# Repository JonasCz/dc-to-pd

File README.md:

# 10 - 60v input 60w DC to USB-C PD buck-boost converter module using TPS25740B and LM5118

**Status:** 

works, but **poor performance**: excessive (maybe - ?) ripple, especially in boost mode and at higher power levels. Mac laptop charges sucessfully off of it, sometimes. Diodes and inductor heats too much (80c at full load). This might be a straightforward fix, or a more siginficant design error (wrong component choice, values, or layout...)

**Why:**

The goal is that I can charge my laptop off an ebike battery directly, or any other DC source (solar system). No other solution that accepts this high input voltage in existence when I started this, now there is YZ826S from china which does the same thing (which I'll try before continueing to work on this project).

**Prototype:**

**Features:**

* Done in Kicad 6.
* Single-sided board for easy assembly.
* The single-sidedness means that it may be possible in a future revision to replace the remaining THT parts with SMD, and then attach a heatsink or enclosure to the back, for through-the-board cooling.
* As compact as possible.
* Input protection:
     * Reverse-polarity protection provided by two high-side n-channel mosfets back-to-back, driven by HT0440.
     * Inrush current limiting provided by same mosfets, by slowing the switch-on speed significantly.
     * Fuse
     * both of these work well, I will reuse this in other designs.
* Low standby / idle power consumption: the buck-boost converter is disabled when no device (power consumer) connected.
* Adjustable low-voltage cutout.
* Datasheet implementations for TPS25740B and LM5118 are mostly folowed, only the input protection, 5v supply, and power-saving stuff has some clever stuff.
* XT60 power connectors.
* Status indicator LED.

**Warning:** 

TPS25740B seems to be discontinued with no obvious replacement. I had to buy them on Aliexpress. Has some minor bugs (I forgot what exactly. Notably needs an additional / different mosfet somewhere. I'll update this when I find my prototype board where I bodged it on. Also requires one cap around LM5118 replaced with different value).

Play with this at your own risk..

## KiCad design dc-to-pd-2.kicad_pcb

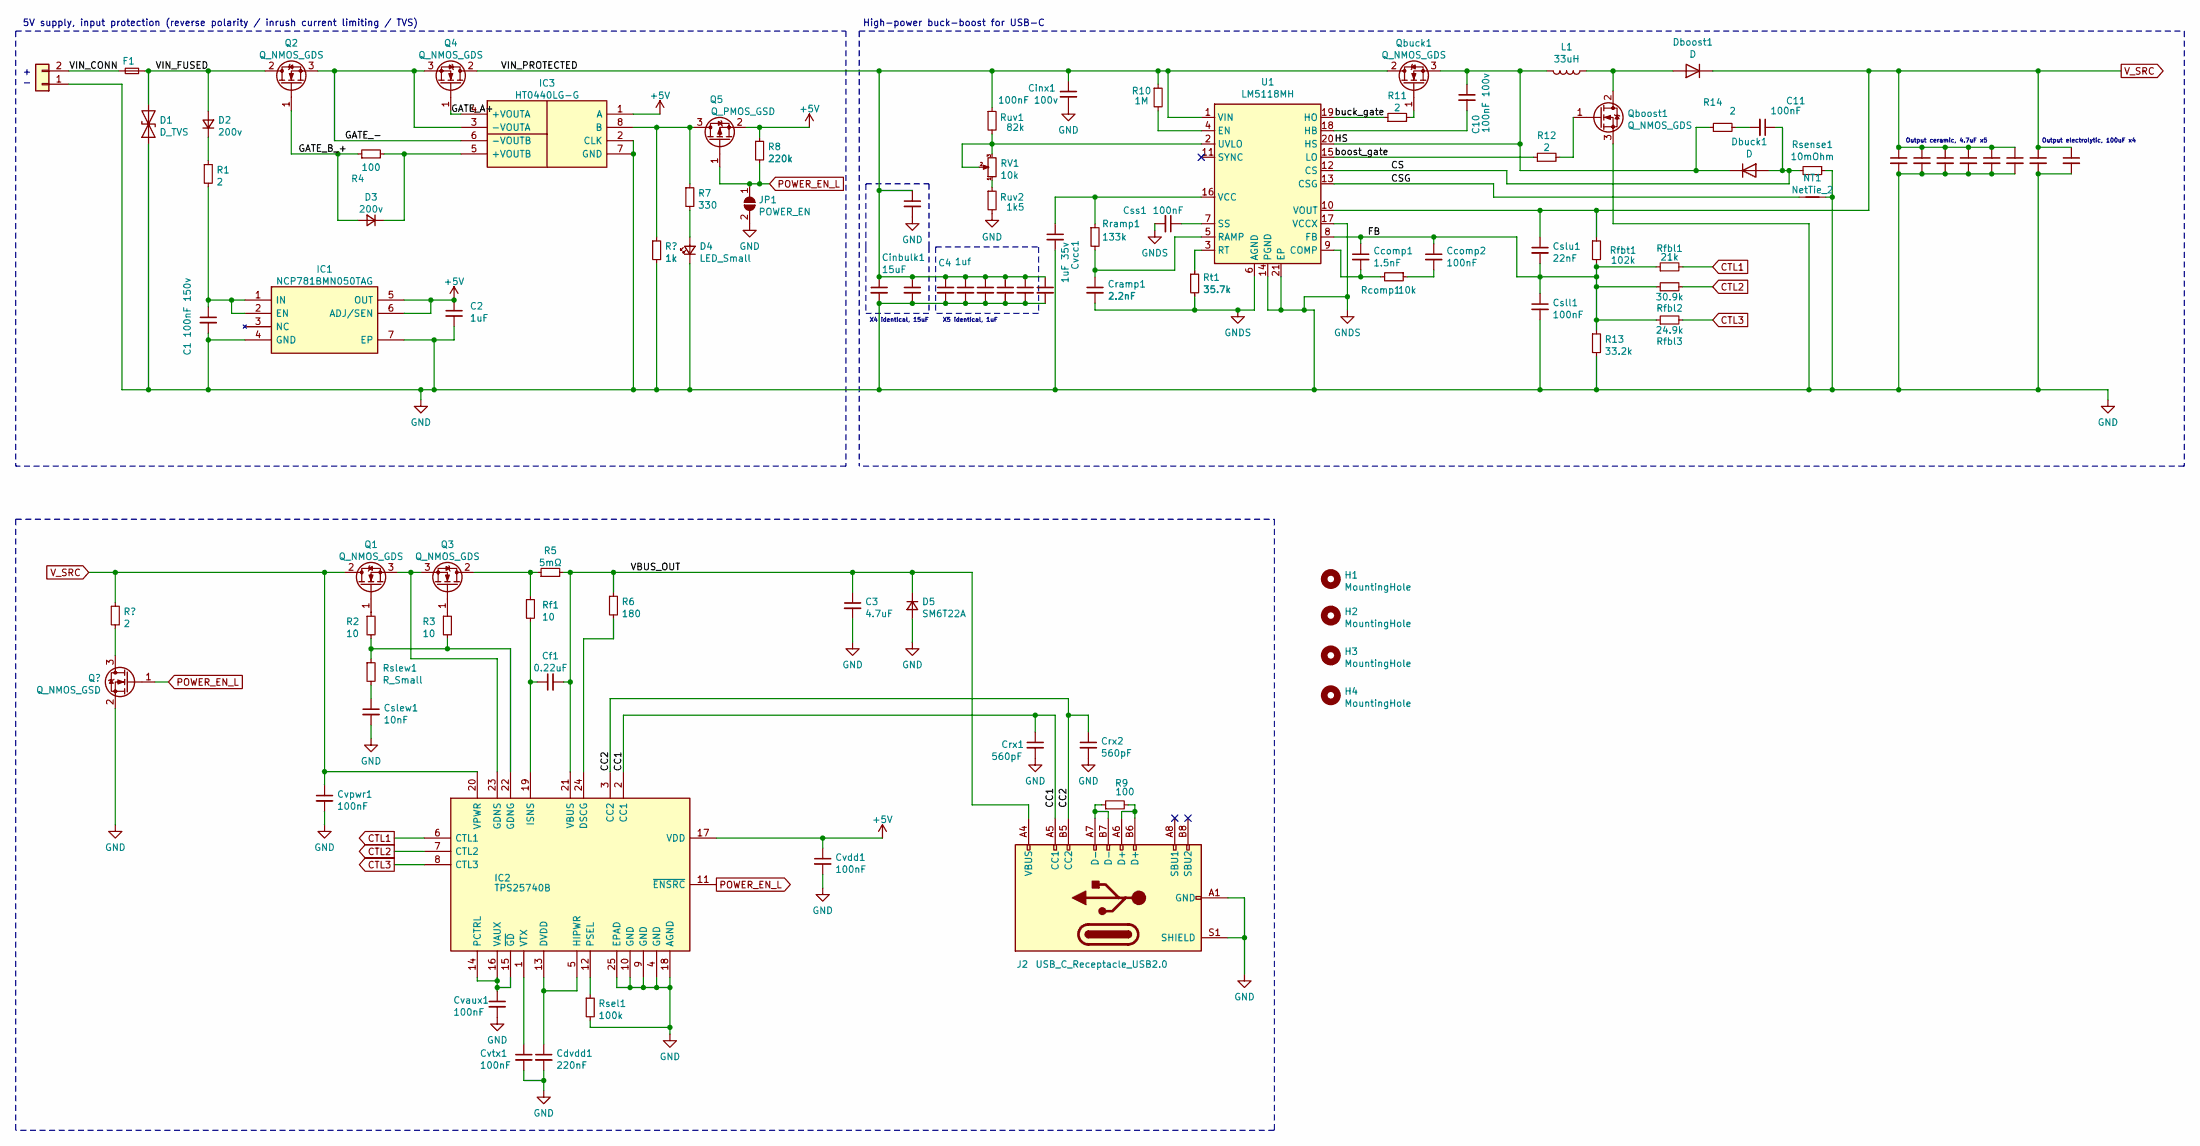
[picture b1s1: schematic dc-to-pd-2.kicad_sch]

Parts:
C1: 100nF 150v; C_1206_3216Metric
C2: 1uF; C_0603_1608Metric
C3, C12, C13, C14, C15, C16, C17: 4.7uF; C_1206_3216Metric; LCSC Part Number C513768
C4, C5, C6, C7, C8, C9: 1uf; C_1206_3216Metric; LCSC Part Number C840122
C10: 100nF 100v; C_0603_1608Metric; LCSC Part Number C840116
C11: 100nF; C_0603_1608Metric; LCSC Part Number C525301
Ccomp1: 1.5nF; C_0603_1608Metric; LCSC Part Number C282745
Ccomp2: 100nF; C_0603_1608Metric; LCSC Part Number C840116
Cdvdd1: 220nF; C_0603_1608Metric
Cf1: 0.22uF; C_0603_1608Metric
Cinbulk1, Cinbulk2, Cinbulk3: 15uF; CP_Radial_D10.0mm_P5.00mm; Mouser Part Number 667-80SXE27MX
Cinx1: 100nF 100v; C_0603_1608Metric; LCSC Part Number C840116
Cout1: 180uf; CP_Radial_D8.0mm_P3.50mm; Mouser Part Number 661-APSG250E181MH08S; LCSC Part Number C239314
Cout2: 180uf; CP_Radial_D8.0mm_P3.50mm; Mouser Part Number 661-APSG250E181MH08S
Cramp1: 2.2nF; C_0603_1608Metric; LCSC Part Number C376966
Crx1, Crx2: 560pF; C_0603_1608Metric
Cslew1: 10nF; C_0603_1608Metric
Csll1: 100nF; C_0603_1608Metric
Cslu1: 22nF; C_0603_1608Metric
Css1: 100nF; C_0603_1608Metric; LCSC Part Number C525301
Cvaux1: 100nF; C_0603_1608Metric
Cvcc1: 1uF 35v; C_0603_1608Metric; LCSC Part Number C28323
Cvdd1: 100nF; C_0603_1608Metric
Cvpwr1: 100nF; C_0603_1608Metric
Cvtx1: 100nF; C_0603_1608Metric
D1: D_TVS; D_SMC; LCSC Part Number C406216
D2, D3: 200v; D_SOD-123
D4: LED_Small; LED_0805_2012Metric
D5: SM6T22A; D_SMB; LCSC Part Number C283616
Dboost1: D; TO-252-2; LCSC Part Number C328574
Dbuck1: D; TO-252-2; LCSC Part Number C328574
F1: Fuse_Small; F_SMD_6.1_2.6; LCSC Part Number C182978
H1, H2, H3, H4: MountingHole; MountingHole_2.2mm_M2_DIN965_Pad
IC1: NCP781BMN050TAG; Manufacturer_Part_Number NCP781BMN050TAG; Mouser Part Number 863-NCP781BMN050TAG
IC2: TPS25740B; TI_VQFN_24_EP_2.7; Manufacturer_Part_Number TPS25740BRGER; Mouser Part Number 595-TPS25740BRGER
IC3: HT0440LG-G; SOIC-8_3.9x4.9mm_P1.27mm; Manufacturer_Part_Number HT0440LG-G; Mouser Part Number 689-HT0440LG-G
J1: Conn_01x02; Amass_XT60PW-M_Kombifootprint; LCSC Part Number C98732
J2: USB_C_Receptacle_USB2.0; USB_C_Receptacle_Palconn_UTC16-G
JP1: POWER_EN; SolderJumper-2_P1.3mm_Open_RoundedPad1.0x1.5mm
L1: 33uH; L_18x16.9_P12.5x4; LCSC Part Number C357282
NT1: NetTie_2; NetTie-2_SMD_Pad0.5mm
Q1, Q3: Q_NMOS_GDS; TO-252-2; LCSC Part Number C845608
Q2: Q_NMOS_GDS; TO-252-2; Mouser Part Number 942-IRFS4115TRLPBF
Q4: Q_NMOS_GDS; TO-252-2; Mouser Part Number 942-IRFS4115TRLPBF; LCSC Part Number C845608
Q5: Q_PMOS_GSD; SOT-23; LCSC Part Number C845585
Qboost1: Q_NMOS_GDS; TO-252-2; LCSC Part Number C845608
Qbuck1: Q_NMOS_GDS; TO-252-2; LCSC Part Number C845608
R1: 2; R_1210_3225Metric
R2, R3: 10; R_0603_1608Metric
R4, R9: 100; R_0603_1608Metric
R5: 5mΩ; R_2512_6332Metric; LCSC Part Number C457120
R6: 180; R_0603_1608Metric
R7: 330; R_0603_1608Metric
R8: 220k; R_0603_1608Metric
R10: 1M; R_0603_1608Metric; LCSC Part Number C23107
R11, R12, R14: 2; R_0603_1608Metric; LCSC Part Number C168306
R13: 33.2k; R_0603_1608Metric; LCSC Part Number C23003
RV1: 10k; Potentiometer_Bourns_3296P_Horizontal
Rcomp1: 10k; R_0603_1608Metric; LCSC Part Number C25804
Rf1: 10; R_0603_1608Metric
Rfbl1: 21k; R_0603_1608Metric; LCSC Part Number C22956
Rfbl2: 30.9k; R_0603_1608Metric; LCSC Part Number C23022
Rfbl3: 24.9k; R_0603_1608Metric; LCSC Part Number C163888
Rfbt1: 102k; R_0603_1608Metric; LCSC Part Number C170436
Rramp1: 133k; R_0603_1608Metric; LCSC Part Number C321714
Rsel1: 100k; R_0603_1608Metric
Rsense1: 10mOhm; R_2512_6332Metric; LCSC Part Number C105370
Rslew1: R_Small; R_0603_1608Metric
Rt1: 35.7k; R_0603_1608Metric; LCSC Part Number C23091
Ruv1: 82k; R_0603_1608Metric; LCSC Part Number C23107
Ruv2: 1k5; R_0603_1608Metric; LCSC Part Number C23107
U1: LM5118MH; Texas_PWP0020A; LCSC Part Number C55878

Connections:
+5V: C2.1, Cvdd1.1, IC1.5 (OUT), IC1.6 (ADJ/SEN), IC2.17 (VDD), IC3.1 (A), Q5.2 (S), R8.1
/CC1: Crx1.1, IC2.2 (CC1), J2.A5 (CC1)
/CC2: Crx2.1, IC2.3 (CC2), J2.B5 (CC2)
/CS: C11.1, Dbuck1.2 (A), Rsense1.2, U1.12 (CS)
/CSG: NT1.1, U1.13 (CSG)
/FB: Ccomp1.1, Ccomp2.1, Csll1.1, Cslu1.2, R13.1, Rfbl1.1, Rfbl2.1, Rfbl3.1, Rfbt1.2, U1.8 (FB)
/GATE_-: IC3.3 (-VOUTA), IC3.6 (-VOUTB), Q2.3 (S), Q4.3 (S)
/GATE_A+: IC3.4 (+VOUTA), Q4.1 (G)
/GATE_B_+: D3.2 (A), Q2.1 (G), R4.1
/HS: C10.1, Dbuck1.1 (K), L1.2, Qbuck1.3 (S), R14.1, U1.20 (HS)
/VBUS_OUT: C3.1, Cf1.2, D5.1 (K), IC2.21 (VBUS), J2.A4 (VBUS), J2.A9 (VBUS), J2.B4 (VBUS), J2.B9 (VBUS), R5.2, R6.1
/VIN_CONN: F1.2, J1.2
/VIN_FUSED: D1.2 (A2), D2.2 (A), F1.1, Q2.2 (D)
/VIN_PROTECTED: C4.1, C5.1, C6.1, C7.1, C8.1, C9.1, Cinbulk1.1, Cinbulk2.1, Cinbulk3.1, Cinx1.1, Q4.2 (D), Qbuck1.2 (D), R10.1, Ruv1.1, U1.1 (VIN)
/boost_gate: R12.1, U1.15 (LO)
/buck_gate: R11.1, U1.19 (HO)
CTL1: IC2.6 (CTL1), Rfbl1.2
CTL2: IC2.7 (CTL2), Rfbl2.2
CTL3: IC2.8 (CTL3), Rfbl3.2
GND: C1.2, C2.2, C3.2, C4.2, C5.2, C6.2, C7.2, C8.2, C9.2, C12.2, C13.2, C14.2, C15.2, C16.2, C17.2, Cdvdd1.2, Cinbulk1.2, Cinbulk2.2, Cinbulk3.2, Cinx1.2, Cout1.2, Cout2.2, Cramp1.2, Crx1.2, Crx2.2, Cslew1.2, Csll1.2, Css1.2, Cvaux1.2, Cvcc1.2, Cvdd1.2, Cvpwr1.2, Cvtx1.2, D1.1 (A1), D4.1 (K), D5.2 (A), H1.1, IC1.4 (GND), IC1.7 (EP), IC2.4 (GND), IC2.9 (GND), IC2.10 (GND), IC2.18 (AGND), IC2.25 (EPAD), IC3.2 (CLK), IC3.7 (GND), J1.1, J2.A1 (GND), J2.A12 (GND), J2.B1 (GND), J2.B12 (GND), J2.S1 (SHIELD), JP1.2 (B), NT1.2, Qboost1.3 (S), R13.2, Rsel1.2, Rsense1.1, Rt1.2, Ruv2.2, U1.6 (AGND), U1.14 (PGND), U1.17 (VCCX), U1.21 (EP)
unnamed: C1.1, IC1.1 (IN), IC1.2 (EN), R1.2
unnamed: C10.2, U1.18 (HB)
unnamed: C11.2, R14.2
unnamed: Ccomp1.2, Rcomp1.2, U1.9 (COMP)
unnamed: Ccomp2.2, Rcomp1.1
unnamed: Cdvdd1.1, IC2.5 (HIPWR), IC2.13 (DVDD)
unnamed: Cf1.1, IC2.19 (ISNS), Rf1.2
unnamed: Cramp1.1, Rramp1.2, U1.5 (RAMP)
unnamed: Cslew1.1, Rslew1.2
unnamed: Css1.1, U1.7 (SS)
unnamed: Cvaux1.1, IC2.14 (PCTRL), IC2.15 (~GD), IC2.16 (VAUX)
unnamed: Cvcc1.1, Rramp1.1, U1.16 (VCC)
unnamed: Cvtx1.1, IC2.1 (VTX)
unnamed: D2.1 (K), R1.1
unnamed: D3.1 (K), IC3.5 (+VOUTB), R4.2
unnamed: D4.2 (A), R7.2
unnamed: Dboost1.2 (A), L1.1, Qboost1.2 (D)
unnamed: IC2.12 (PSEL), Rsel1.1
unnamed: IC2.22 (GDNG), R2.2, R3.2, Rslew1.1
unnamed: IC2.23 (GDNS), Q1.3 (S), Q3.3 (S)
unnamed: IC2.24 (DSCG), R6.2
unnamed: IC3.8 (B), Q5.3 (D), R7.1
unnamed: J2.A6 (D+), J2.B6 (D+), R9.2
unnamed: J2.A7 (D-), J2.B7 (D-), R9.1
unnamed: Q1.1 (G), R2.1
unnamed: Q3.1 (G), R3.1
unnamed: Q3.2 (D), R5.1, Rf1.1
unnamed: Qboost1.1 (G), R12.2
unnamed: Qbuck1.1 (G), R11.2
unnamed: R10.2, U1.4 (EN)
unnamed: RV1.1, Ruv2.1
unnamed: RV1.2, RV1.3, Ruv1.2, U1.2 (UVLO)
unnamed: Rt1.1, U1.3 (RT)
POWER_EN_L: IC2.11 (~ENSRC), JP1.1 (A), Q5.1 (G), R8.2
V_SRC: C12.1, C13.1, C14.1, C15.1, C16.1, C17.1, Cout1.1, Cout2.1, Cslu1.1, Cvpwr1.1, Dboost1.1 (K), IC2.20 (VPWR), Q1.2 (D), Rfbt1.1, U1.10 (VOUT)

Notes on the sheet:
5V supply, input protection (reverse polarity / inrush current limiting / TVS)
+ -
High-power buck-boost for USB-C
X4 identical, 15uF
X5 identical, 1uF
Output ceramic, 4.7uF x5
Output electrolytic, 100uF x4

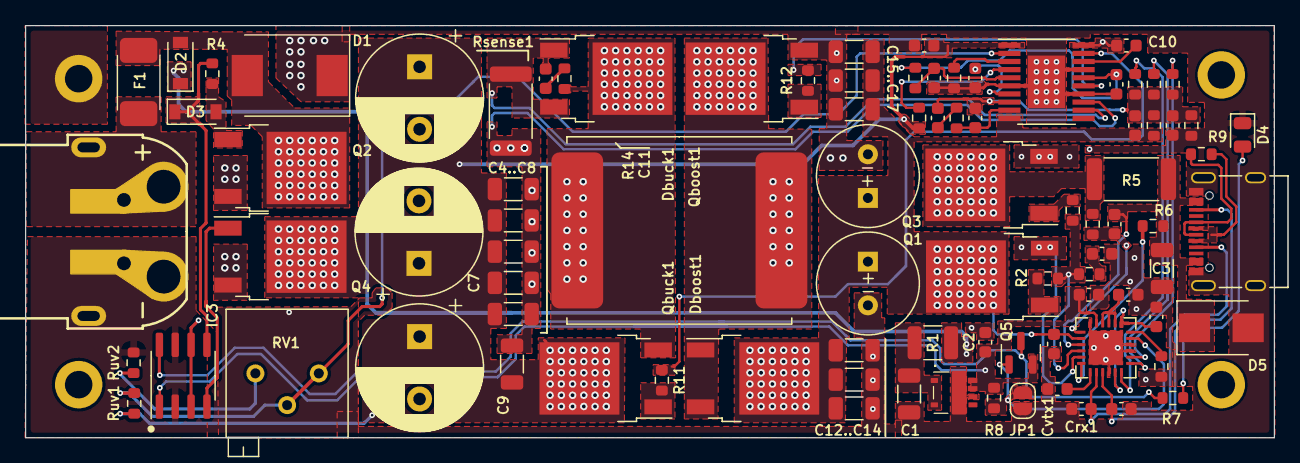
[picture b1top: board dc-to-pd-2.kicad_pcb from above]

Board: 4 copper layers, 100.0 x 33.0 mm, 95 parts (1 on the bottom side), 55 nets.

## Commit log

2022-06-04 add readme
2022-06-04 add photo
2022-06-07 .DS_Store banished!
2022-07-13 kill .DS_Store
